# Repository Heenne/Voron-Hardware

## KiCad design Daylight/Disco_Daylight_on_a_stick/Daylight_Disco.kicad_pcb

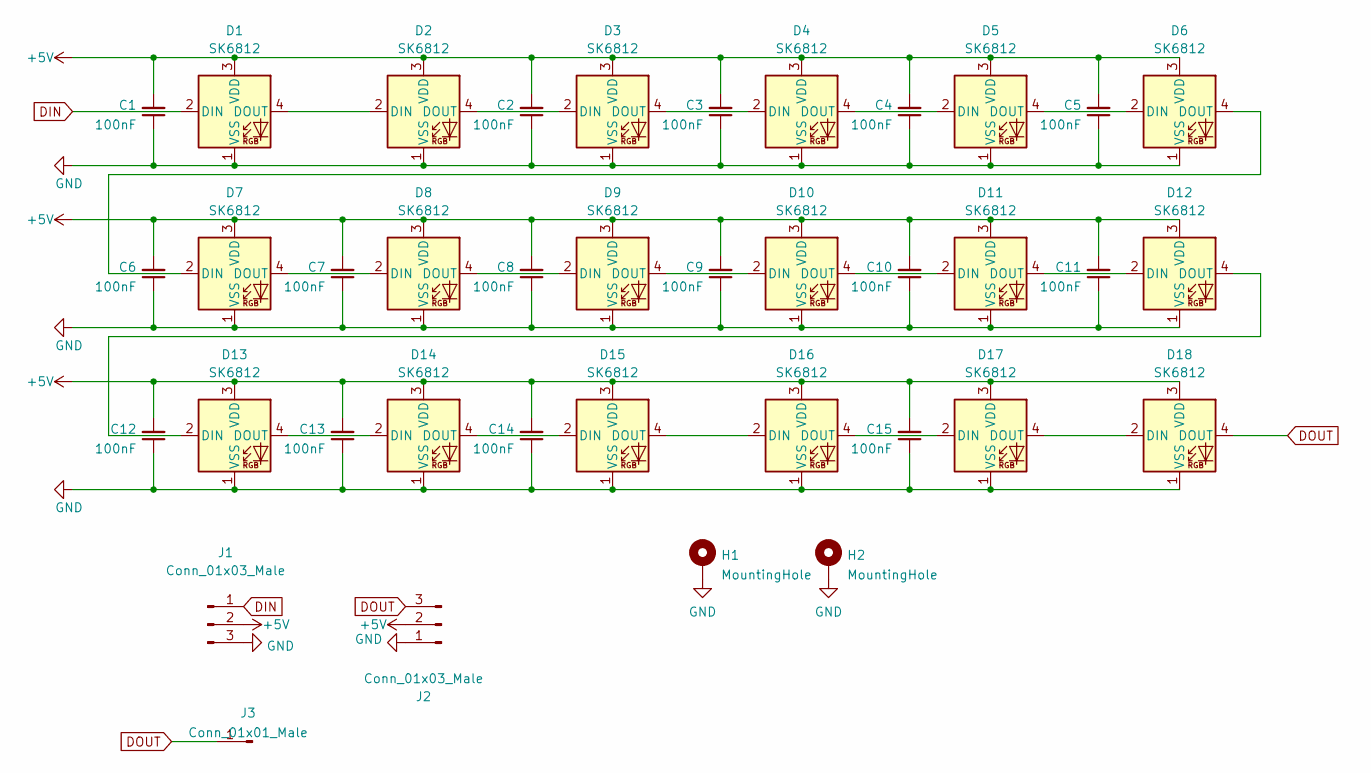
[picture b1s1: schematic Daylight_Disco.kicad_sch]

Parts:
C1, C2, C3, C4, C5, C6, C7, C8, C9, C10, C11, C12, C13, C14, C15: 100nF; C_0805_2012Metric_Pad1.18x1.45mm_HandSolder
D1, D2, D3, D4, D5, D6, D7, D8, D9, D10, D11, D12, D13, D14, D15, D16, D17, D18: SK6812; LED_SK6812_PLCC4_5.0x5.0mm_P3.2mm
H1, H2: MountingHole; MountingHole_3.2mm_M3_Pad_Via
J1, J2: Conn_01x03_Male; JST_XH_S3B-XH-A-1_1x03_P2.50mm_Horizontal
J3: Conn_01x01_Male; PinHeader-1-with-SMDpad

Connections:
+5V: C1.2, C2.2, C3.2, C4.2, C5.2, C6.2, C7.2, C8.2, C9.2, C10.2, C11.2, C12.2, C13.2, C14.2, C15.2, D1.3 (VDD), D2.3 (VDD), D3.3 (VDD), D4.3 (VDD), D5.3 (VDD), D6.3 (VDD), D7.3 (VDD), D8.3 (VDD), D9.3 (VDD), D10.3 (VDD), D11.3 (VDD), D12.3 (VDD), D13.3 (VDD), D14.3 (VDD), D15.3 (VDD), D16.3 (VDD), D17.3 (VDD), D18.3 (VDD), J1.2, J2.2
DIN: D1.2 (DIN), J1.1
DOUT: D18.4 (DOUT), J2.3, J3.1
GND: C1.1, C2.1, C3.1, C4.1, C5.1, C6.1, C7.1, C8.1, C9.1, C10.1, C11.1, C12.1, C13.1, C14.1, C15.1, D1.1 (VSS), D2.1 (VSS), D3.1 (VSS), D4.1 (VSS), D5.1 (VSS), D6.1 (VSS), D7.1 (VSS), D8.1 (VSS), D9.1 (VSS), D10.1 (VSS), D11.1 (VSS), D12.1 (VSS), D13.1 (VSS), D14.1 (VSS), D15.1 (VSS), D16.1 (VSS), D17.1 (VSS), D18.1 (VSS), H1.1, H2.1, J1.3, J2.1
unnamed: D1.4 (DOUT), D2.2 (DIN)
unnamed: D2.4 (DOUT), D3.2 (DIN)
unnamed: D3.4 (DOUT), D4.2 (DIN)
unnamed: D4.4 (DOUT), D5.2 (DIN)
unnamed: D5.4 (DOUT), D6.2 (DIN)
unnamed: D6.4 (DOUT), D7.2 (DIN)
unnamed: D7.4 (DOUT), D8.2 (DIN)
unnamed: D8.4 (DOUT), D9.2 (DIN)
unnamed: D9.4 (DOUT), D10.2 (DIN)
unnamed: D10.4 (DOUT), D11.2 (DIN)
unnamed: D11.4 (DOUT), D12.2 (DIN)
unnamed: D12.4 (DOUT), D13.2 (DIN)
unnamed: D13.4 (DOUT), D14.2 (DIN)
unnamed: D14.4 (DOUT), D15.2 (DIN)
unnamed: D15.4 (DOUT), D16.2 (DIN)
unnamed: D16.4 (DOUT), D17.2 (DIN)
unnamed: D17.4 (DOUT), D18.2 (DIN)

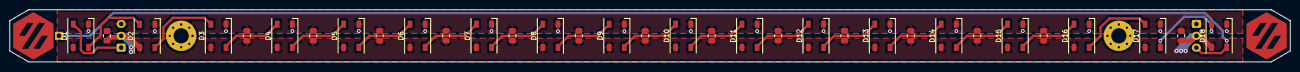
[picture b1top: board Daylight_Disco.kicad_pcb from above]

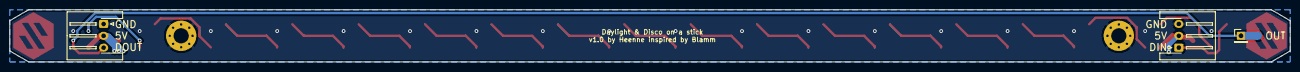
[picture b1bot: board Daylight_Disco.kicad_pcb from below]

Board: 2 copper layers, 270.0 x 11.0 mm, 38 parts (3 on the bottom side), 21 nets.

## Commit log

2023-06-30 Changed WS2812B to SK6812 in schematic
2023-07-01 Finished first version of the Daylight & Disco Sticks. Turned all leds by 90°. Rerouted tracks to be more efficient. Ordered first verison of this from jlcpcb.
